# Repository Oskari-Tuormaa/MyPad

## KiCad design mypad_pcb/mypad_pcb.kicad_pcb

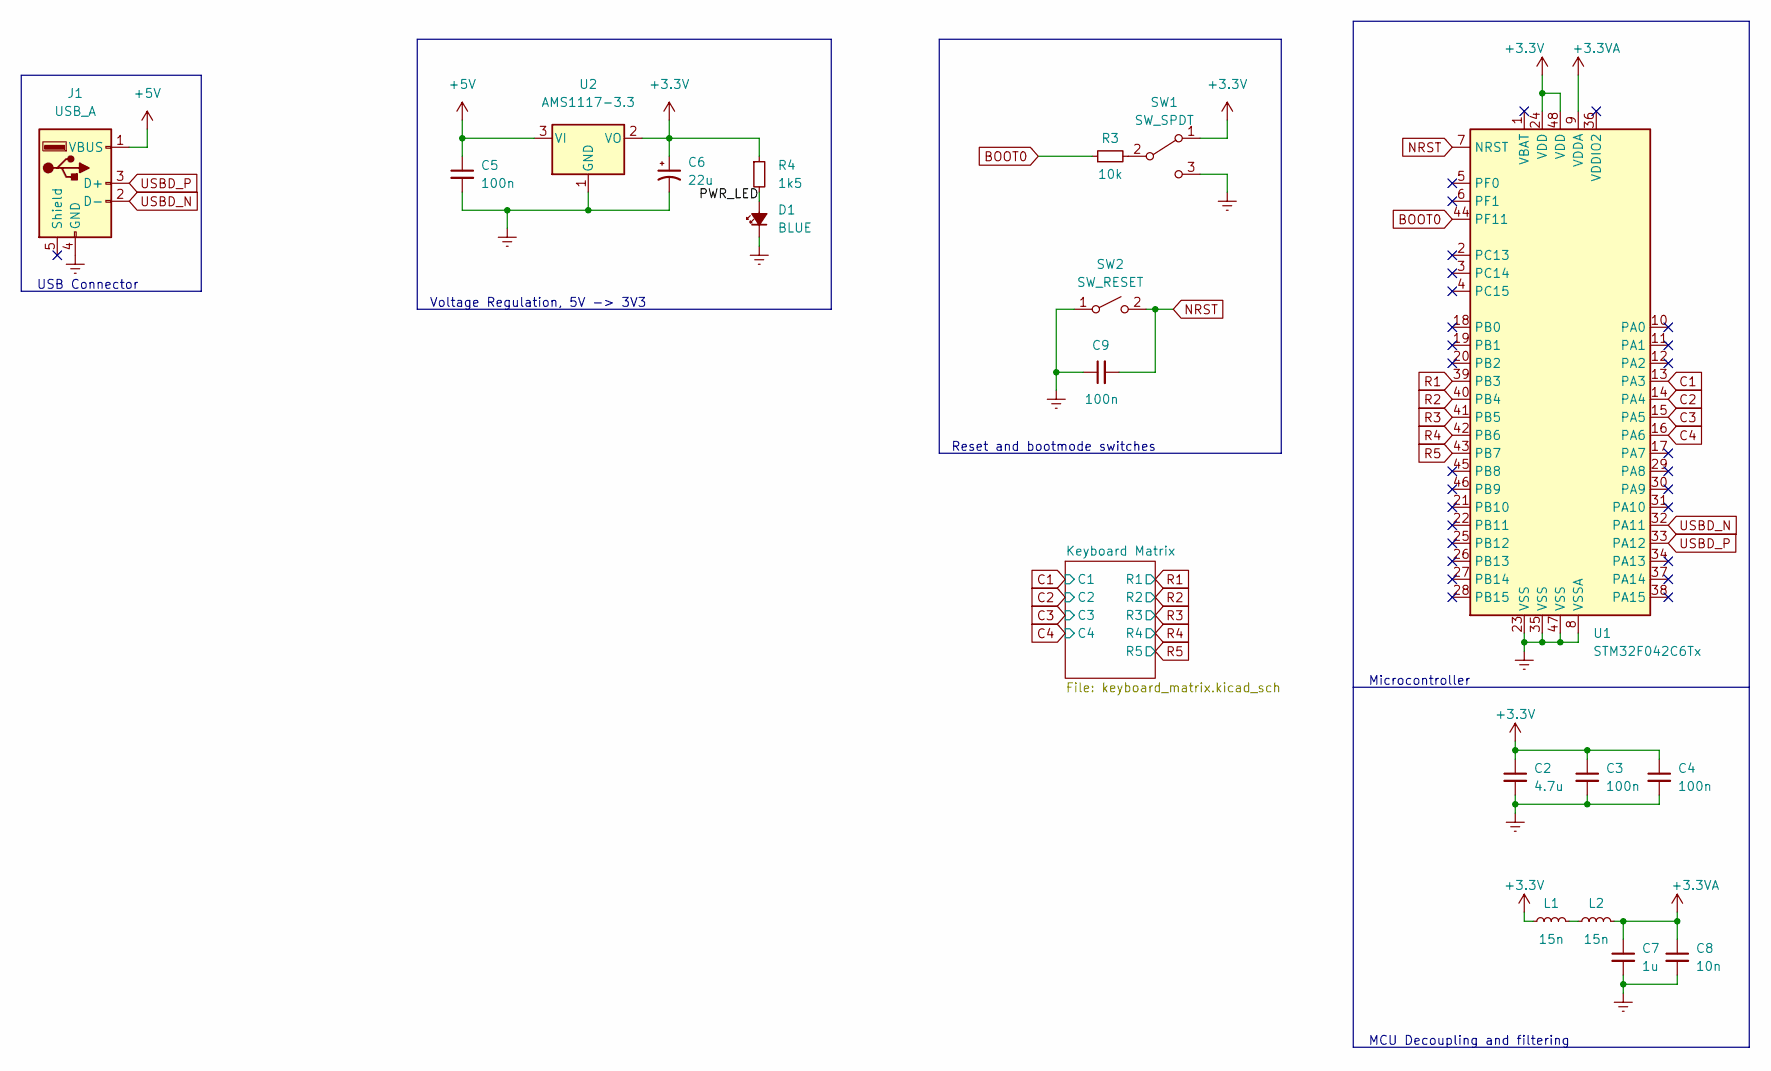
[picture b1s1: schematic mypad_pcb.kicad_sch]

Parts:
C2: 4.7u; C_0805_2012Metric
C3, C4, C5, C9: 100n; C_0603_1608Metric
C6: 22u; CP_EIA-3216-18_Kemet-A
C7: 1u; C_0603_1608Metric
C8: 10n; C_0603_1608Metric
D1: BLUE; LED_0603_1608Metric
J1: USB_A; USB_A_CONNFLY_DS1095-WNR0
L1, L2: 15n; L_0402_1005Metric
R3: 10k; R_0603_1608Metric
R4: 1k5; R_0603_1608Metric
SW1: SW_SPDT; ESP_SPDT_Slide_Switch
SW2: SW_RESET; DTSM31N_SMD_Tact_Switch_4.3mm
U1: STM32F042C6Tx; LQFP-48_7x7mm_P0.5mm
U2: AMS1117-3.3; SOT-223-3_TabPin2

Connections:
+3.3V: C2.1, C3.1, C4.1, C6.1, L1.1, R4.1, SW1.1 (A), U1.24 (VDD), U1.48 (VDD), U2.2 (VO)
+3.3VA: C7.1, C8.1, L2.2, U1.9 (VDDA)
+5V: C5.1, J1.1 (VBUS), U2.3 (VI)
/PWR_LED: D1.2 (A), R4.2
BOOT0: R3.1, U1.44 (PF11)
C1: U1.13 (PA3); also elsewhere on the board
C2: U1.14 (PA4); also elsewhere on the board
C3: U1.15 (PA5); also elsewhere on the board
C4: U1.16 (PA6); also elsewhere on the board
Earth: C2.2, C3.2, C4.2, C5.2, C6.2, C7.2, C8.2, C9.1, D1.1 (K), J1.4 (GND), SW1.3 (C), SW2.1 (A), U1.8 (VSSA), U1.23 (VSS), U1.35 (VSS), U1.47 (VSS), U2.1 (GND)
NRST: C9.2, SW2.2 (B), U1.7 (NRST)
unnamed: L1.2, L2.1
unnamed: R3.2, SW1.2 (B)
R1: U1.39 (PB3); also elsewhere on the board
R2: U1.40 (PB4); also elsewhere on the board
R3: U1.41 (PB5); also elsewhere on the board
R4: U1.42 (PB6); also elsewhere on the board
R5: U1.43 (PB7); also elsewhere on the board
USBD_N: J1.2 (D-), U1.32 (PA11)
USBD_P: J1.3 (D+), U1.33 (PA12)

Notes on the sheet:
Voltage Regulation, 5V -> 3V3
MCU Decoupling and filtering
USB Connector
Reset and bootmode switches
Microcontroller

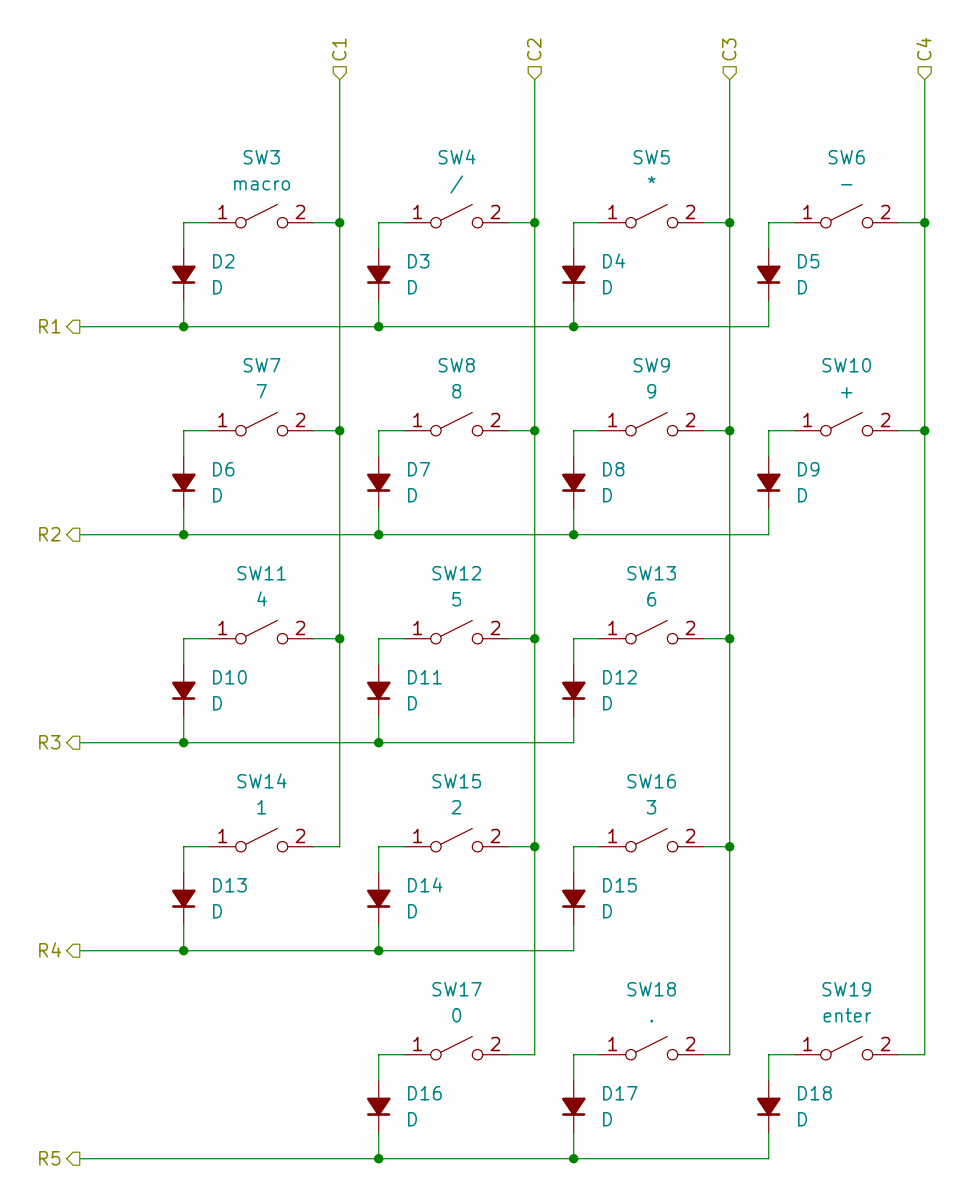
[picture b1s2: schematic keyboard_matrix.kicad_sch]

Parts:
D2, D3, D4, D5, D6, D7, D8, D9, D10, D11, D12, D13, D14, D15, D16, D17, D18: D; D_SOD-123F
SW3: macro; SW_Cherry_MX_PCB_1.00u
SW4: /; SW_Cherry_MX_PCB_1.00u
SW5: *; SW_Cherry_MX_PCB_1.00u
SW6: -; SW_Cherry_MX_PCB_1.00u
SW7: 7; SW_Cherry_MX_PCB_1.00u
SW8: 8; SW_Cherry_MX_PCB_1.00u
SW9: 9; SW_Cherry_MX_PCB_1.00u
SW10: +; SW_Cherry_MX_PCB_2.00u_90deg
SW11: 4; SW_Cherry_MX_PCB_1.00u
SW12: 5; SW_Cherry_MX_PCB_1.00u
SW13: 6; SW_Cherry_MX_PCB_1.00u
SW14: 1; SW_Cherry_MX_PCB_1.00u
SW15: 2; SW_Cherry_MX_PCB_1.00u
SW16: 3; SW_Cherry_MX_PCB_1.00u
SW17: 0; SW_Cherry_MX_PCB_2.00u
SW18: .; SW_Cherry_MX_PCB_1.00u
SW19: enter; SW_Cherry_MX_PCB_2.00u_90deg

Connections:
C1: SW3.2 (B), SW7.2 (B), SW11.2 (B), SW14.2 (B); also elsewhere on the board
C2: SW4.2 (B), SW8.2 (B), SW12.2 (B), SW15.2 (B), SW17.2 (B); also elsewhere on the board
C3: SW5.2 (B), SW9.2 (B), SW13.2 (B), SW16.2 (B), SW18.2 (B); also elsewhere on the board
C4: SW6.2 (B), SW10.2 (B), SW19.2 (B); also elsewhere on the board
unnamed: D2.2 (A), SW3.1 (A)
unnamed: D3.2 (A), SW4.1 (A)
unnamed: D4.2 (A), SW5.1 (A)
unnamed: D5.2 (A), SW6.1 (A)
unnamed: D6.2 (A), SW7.1 (A)
unnamed: D7.2 (A), SW8.1 (A)
unnamed: D8.2 (A), SW9.1 (A)
unnamed: D9.2 (A), SW10.1 (A)
unnamed: D10.2 (A), SW11.1 (A)
unnamed: D11.2 (A), SW12.1 (A)
unnamed: D12.2 (A), SW13.1 (A)
unnamed: D13.2 (A), SW14.1 (A)
unnamed: D14.2 (A), SW15.1 (A)
unnamed: D15.2 (A), SW16.1 (A)
unnamed: D16.2 (A), SW17.1 (A)
unnamed: D17.2 (A), SW18.1 (A)
unnamed: D18.2 (A), SW19.1 (A)
R1: D2.1 (K), D3.1 (K), D4.1 (K), D5.1 (K); also elsewhere on the board
R2: D6.1 (K), D7.1 (K), D8.1 (K), D9.1 (K); also elsewhere on the board
R3: D10.1 (K), D11.1 (K), D12.1 (K); also elsewhere on the board
R4: D13.1 (K), D14.1 (K), D15.1 (K); also elsewhere on the board
R5: D16.1 (K), D17.1 (K), D18.1 (K); also elsewhere on the board

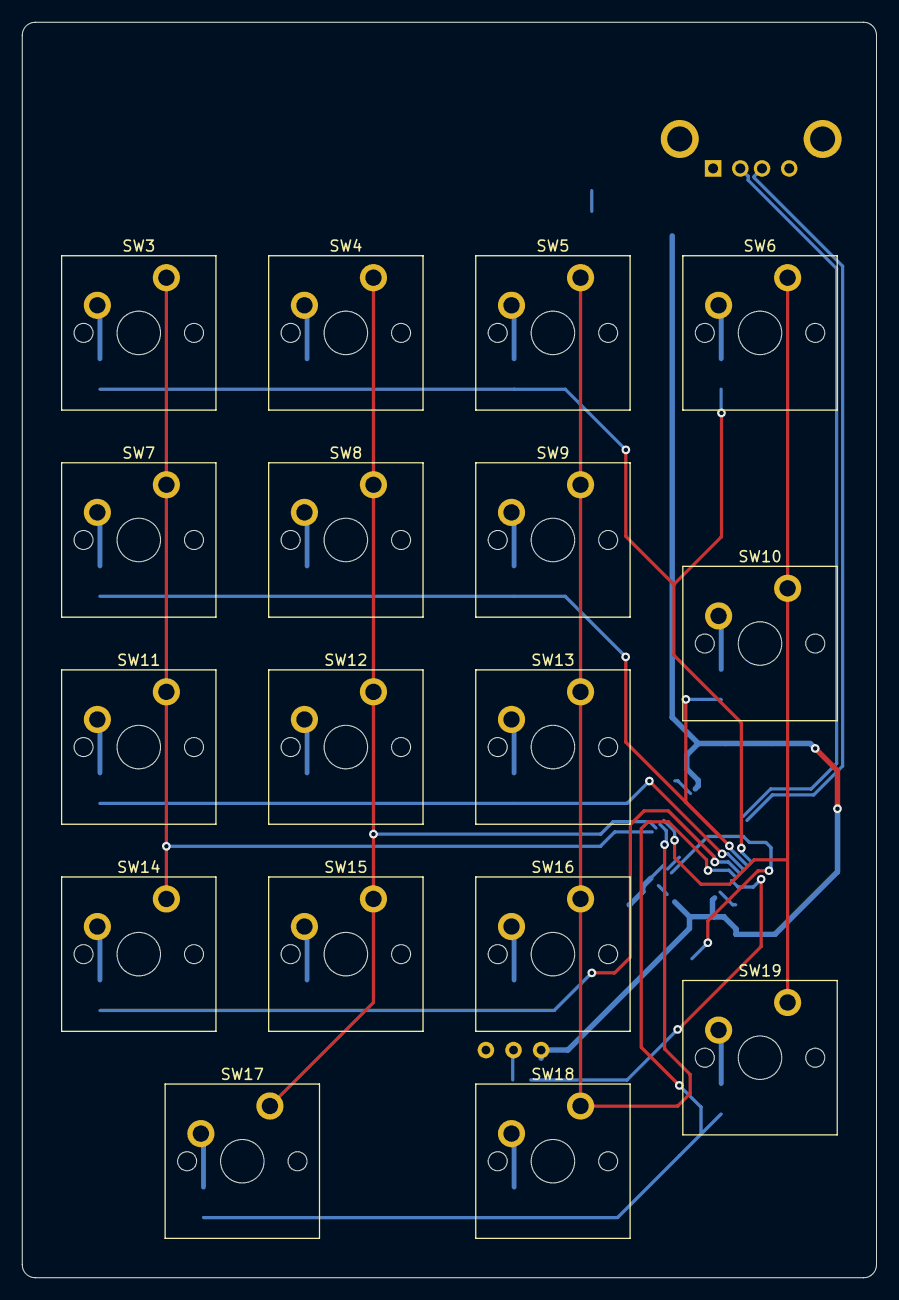
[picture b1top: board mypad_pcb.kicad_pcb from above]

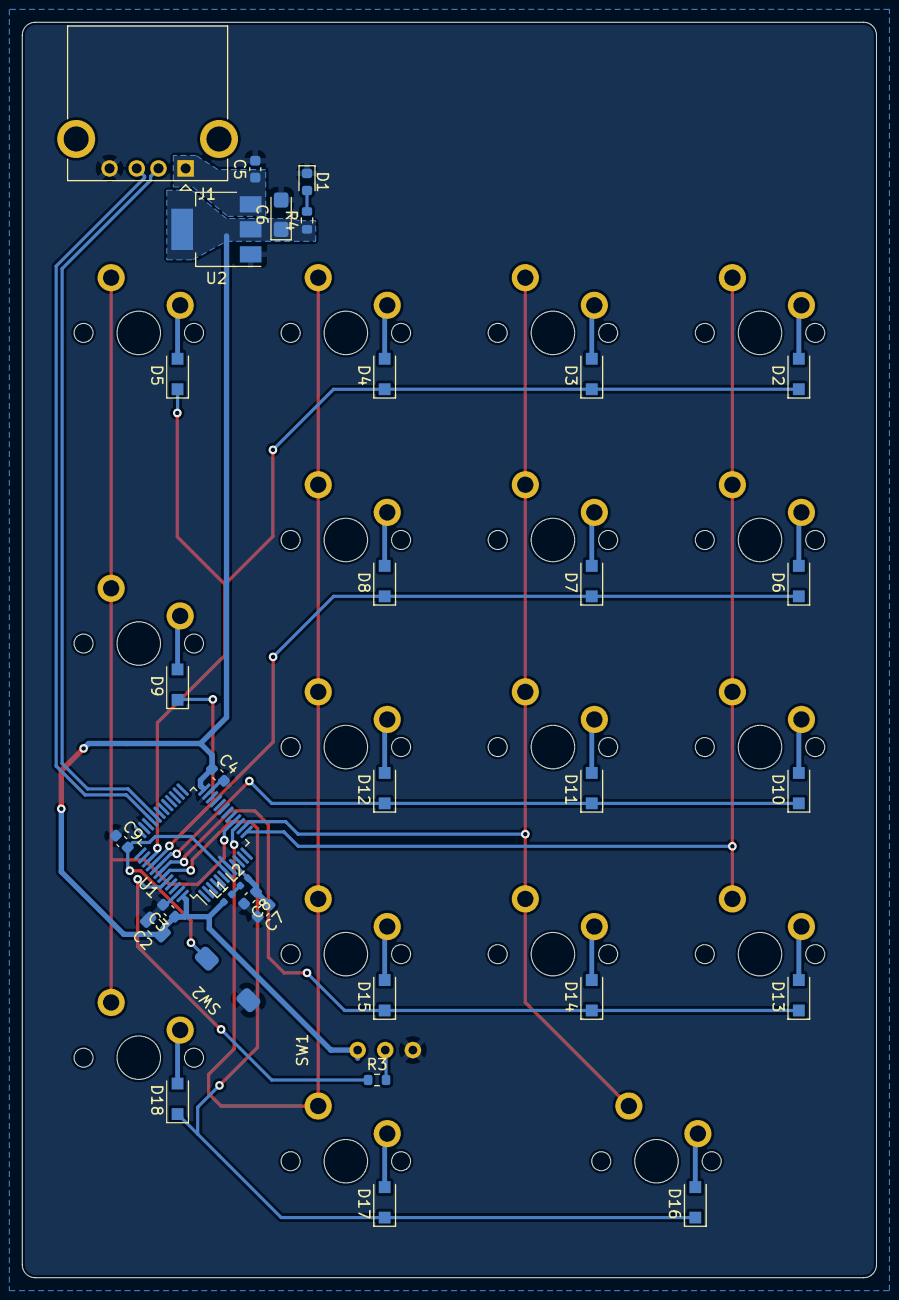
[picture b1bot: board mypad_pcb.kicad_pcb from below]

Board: 2 copper layers, 78.6 x 115.5 mm, 52 parts (35 on the bottom side), 37 nets.

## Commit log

2022-09-13 Add KiCAD PCB files
2022-09-13 Add STM32CubeIDE Project
2022-09-13 Add Keyboard-Layout-Editor json file and GIMP key matrix files
2022-09-13 Add libreoffice calc partslist
2022-09-13 Add .gitignore
2022-09-15 Swap components for STM32F042C6 compatible ones
2022-09-15 Add STM32F042C6T6 literature and JabRef files
2022-09-15 Update STM32 workspace to use STM32F042C6T6
